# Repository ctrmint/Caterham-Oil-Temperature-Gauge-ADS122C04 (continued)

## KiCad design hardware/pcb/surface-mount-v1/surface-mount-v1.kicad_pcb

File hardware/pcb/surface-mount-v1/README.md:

# surface-mount-v1: interface PCB

surface-mount-v1 is the first interface PCB. It's a two-layer board with surface-mount parts, fitted by the board house. It replaces both the veroboard and the separate protection board. It holds:
- the ADS1115 as a bare chip;
- Rp;
- the three input filters;
- the harness protection;
- the I²C pull-ups;
- the 5 V feed.

It plugs straight into the 8-way socket on the back of the Waveshare case, and the case's two bottom screws hold it on. Issue #48.

**Status:** designed, with zero ERC and zero DRC findings. Not yet built or tested; the fit check and bench checks below are owed. Like the rest of the gauge, it's supplementary to the factory warnings ([docs/SAFETY.md](../../../docs/SAFETY.md)).

| | |
|---|---|
| Size | 39 × 23 mm, 783 mm². D-shaped so it sits 1 mm inside the 51 mm case outline: nothing shows around the gauge. For comparison, the veroboard is 66 × 43 mm. |
| Stack-up | 2 layers, 1.6 mm FR-4, 1 oz copper, GND pour on both sides |
| Rules | 0.2 mm clearance, 0.25 mm minimum track, 0.6/0.3 mm vias, 0.5 mm copper to edge. Well inside a standard JLCPCB or PCBWay 2-layer service. |
| Parts | 20 on the board. The board house fits 17 SMD parts; you fit J1, J2 and Rp. |
| Height above the case back | 2.54 mm spacing, then the board, then the J2 header (9.9 mm) and the harness plug |

## Design decisions (from #48)

1. **Vehicle power: a separate automotive 12 V → 5 V converter.** Its 5 V comes in on J2 pin 3 and passes through D4 (SS34) to the display's 5V pin.
   - The display board wires that pin straight to USB-C VBUS and to the AXP2101's input, with no diode (Waveshare schematic).
   - D4 stops USB power feeding back into the converter when both are connected.
   - D4 drops about 0.4 V, which leaves the display inside its 3.9–5.5 V VBUS range.
2. **Mounting: plugged straight into the case socket.** The case's two bottom screws hold the board, through H1/H2, with 2.5 mm spacers.
3. **Protection: PR #34's design, in surface-mount parts.**
   - Each harness tap is two stages: R3/R5 (1 kΩ, 1206), then a BAV99 clamp to 3.3 V and GND, then R4/R6 (1 kΩ). The BAV99 is a 1N4148-class pair, so it leaks nanoamps, not the microamps of a warm Schottky.
   - An SMBJ15A TVS sits on the signal wire. Its breakdown is at least 16.7 V, so it doesn't conduct at 14.4 V.
   - The 100 kΩ break-detect bias stays on the harness side.
4. **Assembly: the board house fits the SMD parts.** The fab files include a JLCPCB-format BOM and placement file. You fit J1, J2 and Rp.
5. **3.3 V for the ADC and Rp: still the display's 3.3V pin, not a local regulator.** I recommended a local regulator in #48 and have reversed that.
   - A wire chafed onto 14.4 V pushes current back into the 3.3 V rail through Rp and the clamps, about 34 mA for the signal wire.
   - A regulator can only source current, so a lightly loaded local rail would rise with the fault and would need its own clamp.
   - The display's rail is the AXP2101's 2 A DCDC1, and the display board's own load absorbs that current.
   - The rail still sees the fault while the gauge is off; see what this board doesn't cover, below.

## Circuit

The measurement is the one in [WIRING.md](../../WIRING.md): Vp = A0 − A3 across Rp, Vs = A3 − A1 across the sender, and Rs = Rp × Vs / Vp. The differences from the veroboard:
- **Every tap is a soldered track.** There's no plug-in module, so the open-tap failure in #39 (a module socket contact lifting) can't happen here.
- **The board carries its own I²C pull-ups (10 kΩ) and 100 nF decoupling.** The display board has no pull-ups on GPIO17/18, and the Adafruit module used to supply them.
- **R2, the A0 tap, is a Kelvin connection to Rp's top pad.** It runs on its own bottom-layer track and joins nothing else on the way.
- **Nothing is in series between Rp and the sender pin.**
- **R7 biases the sense wire on the harness side of R5**, so a broken sense wire still reads `GROUND FAULT`.

`tests/test_surface_mount_v1.py` checks these rules against the design table, and checks J1 against the firmware's pins.

**With a harness wire at 14.4 V:**

| Wire | Into the 3.3 V rail | Dissipation | Into the ADC pin |
|---|---|---|---|
| Signal | about 24 mA through Rp, plus about 10 mA through R3 and D1 | R1 0.26 W (TNPW1206 is rated 0.27 W at film ≤125 °C); R3 0.11 W (1206, 0.25 W) | under 0.5 mA, through R4 |
| Sense | about 10 mA through R5 and D2 | R5 0.11 W | under 0.5 mA, through R6 |

After any such fault, measure Rp again.

## Connectors

The parts list is [BOM.md](BOM.md), also as `surface-mount-v1-bom.csv`. It gives every part with its manufacturer part number, and both connector pinouts.

- **J1, the display header** (Samtec TSW-108-07-G-S, gold):
  - It's fitted on the **bottom** side: its long pins point away from the components and into the case socket.
  - The pin order matches the case label, 18 17 16 RX TX 3.3V G 5V, which is also printed on the top silkscreen.
  - Pin 1 ("18", SCL) has the square pad.
- **J2, the harness** (Molex Micro-Fit 3.0 43650-0415, 1×4 vertical, positive latch):
  - Pins: 1 sender signal, 2 GND, 3 5 V in, 4 ground sense.
  - The mating housing is 43645-0400 with tin 43030 terminals. They take 0.5 mm² (20 AWG) wire with 1.42–1.85 mm insulation; crimp them with the Molex 63819-0000 or a Micro-Fit ratchet crimper.
  - Twist the sender and sense wires together (WIRING.md).

## Fit check before ordering (human)

The positions come from Waveshare's drawing of the cased board (`ESP32-S3-Touch-AMOLED-1.75-B`), not from your unit. Check them with calipers first:

1. **Socket row:** the 8 pins at 2.54 mm pitch, centred left to right, with their centres 18.70 mm below the case centre. Is the socket face flush with the case back? J1's insulator sets a 2.54 mm gap, so a socket that stands proud changes the spacer height.
2. **Bottom screws:** at ±13.75 mm, 14.70 mm below centre.
   - Check they're M2, and measure the length of the originals.
   - The new screws are that length plus 1.6 mm for the board plus the spacer, so they engage the standoffs as far as before and no further.
3. **Overlay check:** print [renders/placement.svg](renders/placement.svg) at 100 % (1 mm grid, case centre at 0,0), or the Gerbers, and lay it on the case back.

If anything differs, change `layout.py` (`J1_Y`, `HOLES`) and rebuild.

## Ordering and assembly

1. **PCB:** upload `fab/surface-mount-v1-gerbers.zip`. Choose 2 layers, 1.6 mm, any colour, and lead-free HASL or ENIG. Five boards is the usual minimum.
2. **Assembly (optional):** top side only. Upload `fab/surface-mount-v1-bom-jlcpcb.csv` and `fab/surface-mount-v1-cpl-jlcpcb.csv`.
   - Board houses and KiCad differ in the zero rotation for some packages, so check every part in the placement preview: U1's pin-1 dot, the stripes on D3 and D4, and the BAV99s.
   - The files leave out J1, J2 and R1.
3. **Hand-fit R1** (Vishay TNPW1206470RBEEA; Digi-Key or Mouser). Measure it first and note the value: it goes in `kPullUpOhms`, with approval (#36).
4. **Hand-fit J2** on the top side.
5. **Hand-fit J1** from the bottom side and solder it on the top.

## Bench checks (human, owed; see docs/VALIDATION.md)

**Readings through the board:**
- Wire a known 120 Ω resistor from J2 pin 1 to a "tank" point, and connect J2 pins 2 and 4 to the same point.
- Then run WIRING.md bench steps 4–10, with J2 standing in for the harness.

**Fault tests:** apply 14.4 V through a 50 mA current limit to J2 pin 1, then to pin 4. Expect no damage and a fault display, and readings that come back correct afterwards (PR #34).

**Retention:** shake test with the screws and spacers fitted.

## What this board doesn't cover

- **A wire chafed onto an always-live feed while the gauge is off** back-powers the 3.3 V rail through Rp.
- **A long load dump on a wire chafed onto the battery feed** can destroy the TVS. If the TVS then fails short, the gauge shows `SENSOR SHORT`.
- **J1 is still a plug contact.** A bad SDA or SCL contact shows as ADC errors (`adc_ok = false`). A bad 3.3V or GND contact shows as supply or ADC faults.
- **It isn't qualified for automotive use.** The bench checks above and the in-car tests (#43) come first.

## What's in this folder

| Path | What it is |
|---|---|
| `README.md` | This page: decisions, fit check, ordering, assembly, checks. Hand-written. |
| `BOM.md`, `surface-mount-v1-bom.csv` | The full parts list: the board, connectors, harness parts and fitting hardware |
| `fab/surface-mount-v1-gerbers.zip` | Gerbers and drill files, to upload to the board house |
| `fab/surface-mount-v1-bom-jlcpcb.csv`, `fab/surface-mount-v1-cpl-jlcpcb.csv` | The board house's assembly BOM and placement file (SMD parts only) |
| `renders/` | `top.png`, `bottom.png`, `iso.png` (3D); `schematic.svg`; `placement.svg` (1 mm grid in case coordinates) |
| `surface-mount-v1.kicad_pro`, `.kicad_sch`, `.kicad_pcb` | The KiCad 10 project |
| `3d/` | The simplified 3D model of J2, for the renders |
| `generator/` | The source: `design.py` (parts, nets, part numbers) and `layout.py` (placement, routing, silkscreen) |
| `build.sh`, `outputs.sha256` | The rebuild script and the hash manifest it writes |

## Rebuilding

`build.sh` (in this folder) regenerates everything here from `generator/`:
- the KiCad schematic and board;
- ERC and DRC, with schematic parity and zone refill. Any finding fails the build.
- the renders, the Gerbers and drill files, the placement file and the BOMs;
- `outputs.sha256`.

It runs KiCad 10.0.8 in its official container through podman or docker; set `KICAD_LOCAL=1` to use a local KiCad 10.0.8. An unchanged design rebuilds byte-for-byte, so a diff means the design changed.

`tests/test_surface_mount_v1.py`, which runs in CI, fails if anything listed in `outputs.sha256` changes without a rebuild.

**Where the design lives:**
- `design.py`: the parts, nets and part numbers.
- `layout.py`: placement, routing and silkscreen, in case coordinates. `renders/placement.svg` shows the same coordinates.

The generator is the source for surface-mount-v1. You can open the KiCad files in KiCad 10, but the next build overwrites them. To take the design over in the KiCad GUI, delete `generator/` and the generator steps from the script.

KiCad has no 3D model for the Micro-Fit header. `3d/Molex_43650-0415_envelope.wrl` is a plain box of the right size for the renders, not Molex's model.

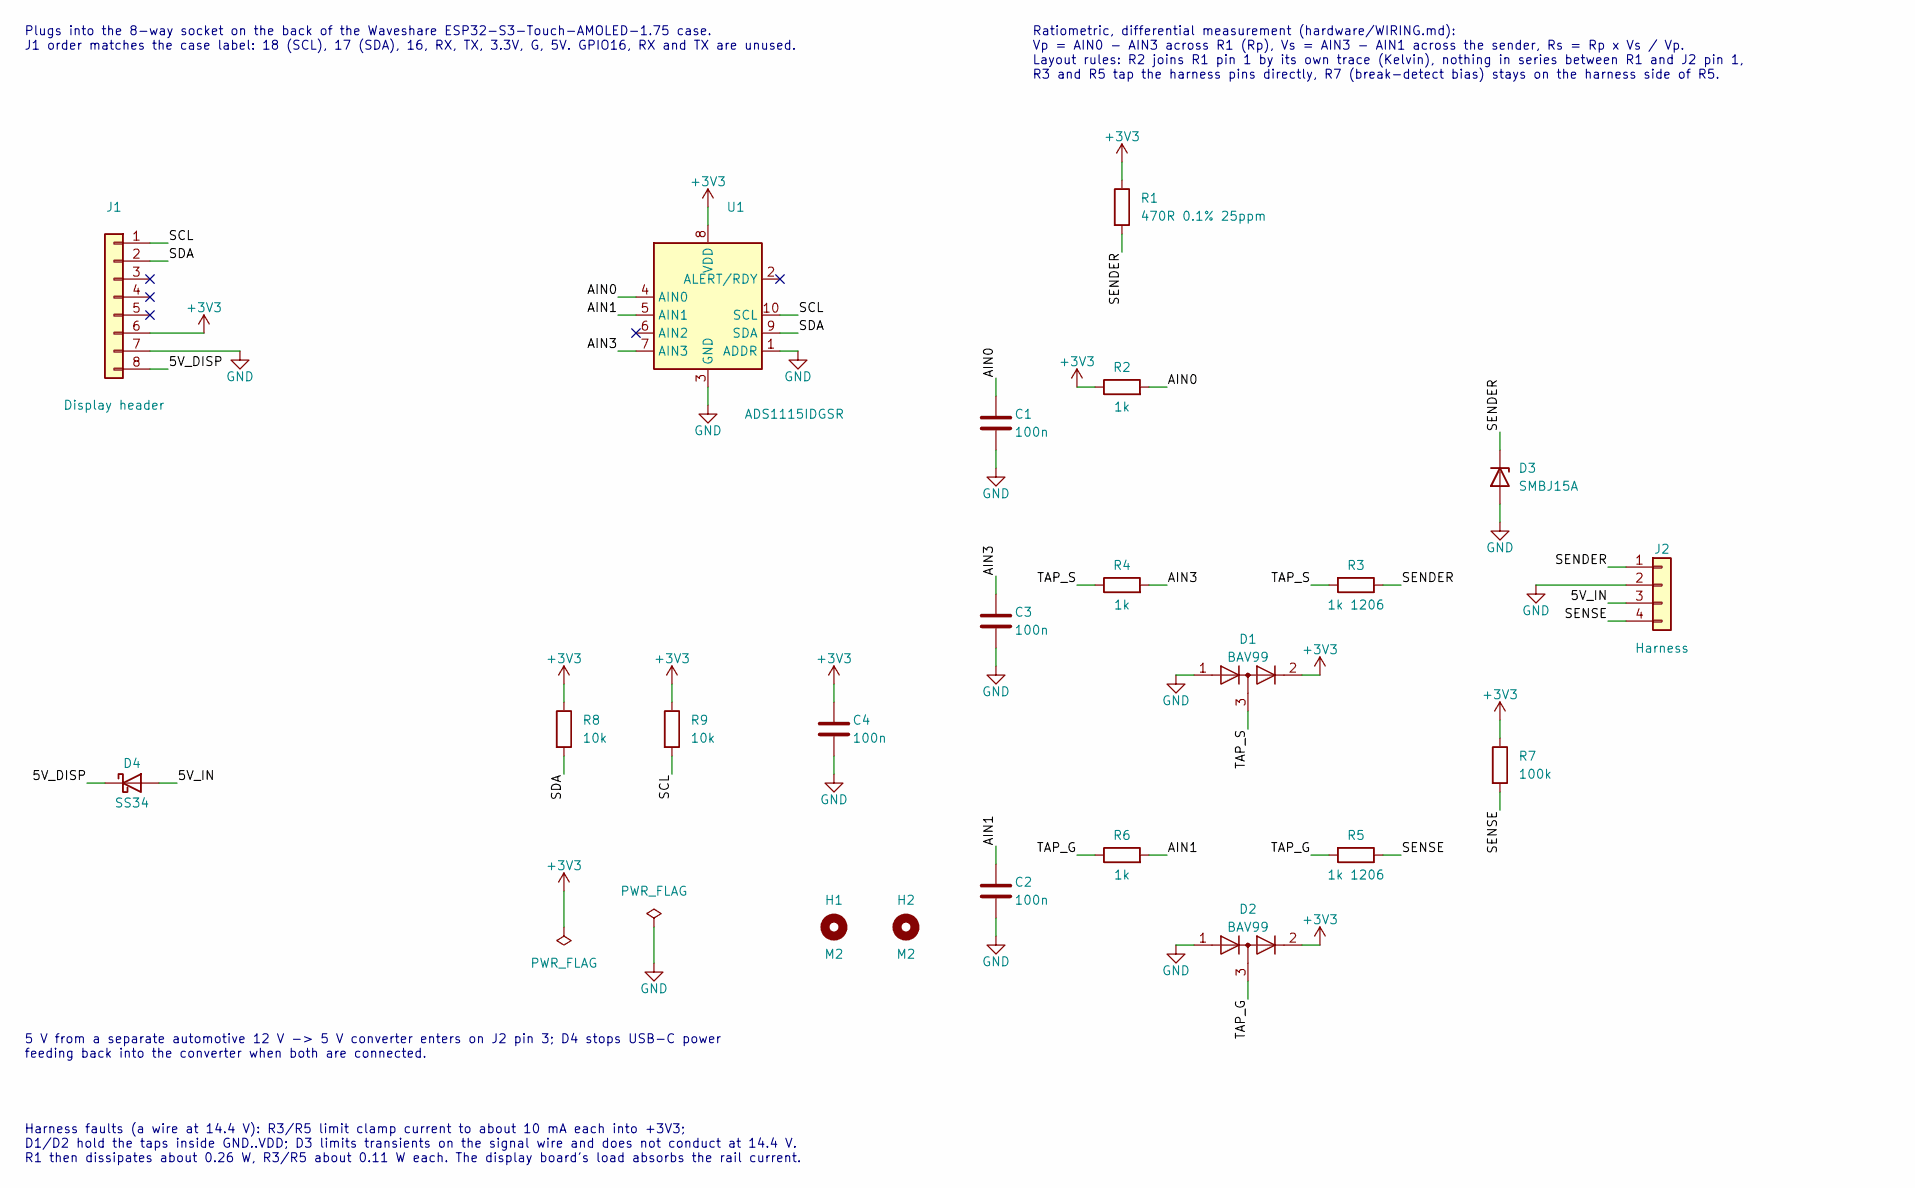
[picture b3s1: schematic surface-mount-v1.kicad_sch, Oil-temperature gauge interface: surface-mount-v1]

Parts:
C1, C2, C3, C4: 100n; C_0603_1608Metric; MPN CC0603KRX7R9BB104; LCSC C14663
D1, D2: BAV99; SOT-23; MPN BAV99,215; LCSC C2500
D3: SMBJ15A; D_SMB; MPN SMBJ15A; LCSC C83846
D4: SS34; D_SMA; MPN SS34; LCSC C8678
H1, H2: M2; MountingHole_2.2mm_M2
J1: Display header; PinHeader_1x08_P2.54mm_Vertical; MPN TSW-108-07-G-S; LCSC C3335496
J2: Harness; Molex_Micro-Fit_3.0_43650-0415_1x04_P3.00mm_Vertical; MPN 43650-0415; LCSC C293547
R1: 470R 0.1% 25ppm; R_1206_3216Metric; MPN TNPW1206470RBEEA
R2, R4, R6: 1k; R_0603_1608Metric; MPN 0603WAF1001T5E; LCSC C21190
R3, R5: 1k 1206; R_1206_3216Metric; MPN 1206W4F1001T5E; LCSC C4410
R7: 100k; R_0603_1608Metric; MPN 0603WAF1003T5E; LCSC C25803
R8, R9: 10k; R_0603_1608Metric; MPN 0603WAF1002T5E; LCSC C25804
U1: ADS1115IDGSR; TSSOP-10_3x3mm_P0.5mm; MPN ADS1115IDGSR; LCSC C37593

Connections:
+3V3: C4.1, D1.2 (A), D2.2 (A), J1.6, R1.1, R2.1, R7.1, R8.1, R9.1, U1.8 (VDD)
/5V_DISP: D4.1 (K), J1.8
/5V_IN: D4.2 (A), J2.3
/AIN0: C1.1, R2.2, U1.4 (AIN0)
/AIN1: C2.1, R6.2, U1.5 (AIN1)
/AIN3: C3.1, R4.2, U1.7 (AIN3)
/SCL: J1.1, R9.2, U1.10 (SCL)
/SDA: J1.2, R8.2, U1.9 (SDA)
/SENDER: D3.1 (K), J2.1, R1.2, R3.1
/SENSE: J2.4, R5.1, R7.2
/TAP_G: D2.3 (K), R5.2, R6.1
/TAP_S: D1.3 (K), R3.2, R4.1
GND: C1.2, C2.2, C3.2, C4.2, D1.1 (K), D2.1 (K), D3.2 (A), J1.7, J2.2, U1.1 (ADDR), U1.3 (GND)

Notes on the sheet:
Plugs into the 8-way socket on the back of the Waveshare ESP32-S3-Touch-AMOLED-1.75 case. J1 order matches the case label: 18 (SCL), 17 (SDA), 16, RX, TX, 3.3V, G, 5V. GPIO16, RX and TX are unused.
Harness faults (a wire at 14.4 V): R3/R5 limit clamp current to about 10 mA each into +3V3; D1/D2 hold the taps inside GND..VDD; D3 limits transients on the signal wire and does not conduct at 14.4 V. R1 then dissipates about 0.26 W, R3/R5 about 0.11 W each. The display board's load absorbs the rai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
5 V from a separate automotive 12 V -> 5 V converter enters on J2 pin 3; D4 stops USB-C power feeding back into the converter when both are connected.
Ratiometric, differential measurement (hardware/WIRING.md): Vp = AIN0 - AIN3 across R1 (Rp), Vs = AIN3 - AIN1 across the sender, Rs = Rp x Vs / Vp. Layout rules: R2 joins R1 pin 1 by its own trace (Kelvin), nothing in series between R1 and J2 pin 1, R3 and R5 tap the harness pins directly, R7 (brea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

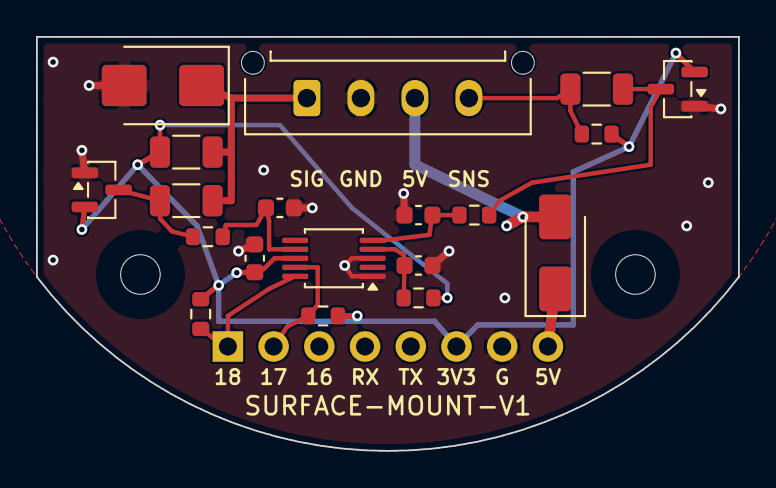
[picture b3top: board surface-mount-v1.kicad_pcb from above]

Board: 2 copper layers, 39.0 x 23.0 mm, 22 parts (1 on the bottom side), 13 nets.

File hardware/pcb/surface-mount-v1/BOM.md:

# surface-mount-v1: parts list

Every part for the surface-mount-v1 interface board and its harness. The same list is in `surface-mount-v1-bom.csv`, and the board-house subset in `fab/surface-mount-v1-bom-jlcpcb.csv`.

Generated by `generator/outputs.py` from `generator/design.py`; edit that, not this file, then run `build.sh`. Part numbers were checked against manufacturer datasheets and distributor pages on 2026-11-15. LCSC numbers are for the board house's assembly service; `hand` parts are fitted by you (see README.md).

## On the board

| Ref | Qty | Value | Package | Manufacturer | MPN | LCSC | Fit | Notes |
|---|---:|---|---|---|---|---|---|---|
| J1 | 1 | Display header | 1x08 2.54 mm THT (bottom side) | Samtec | `TSW-108-07-G-S` | C3335496 | hand | 8-way 2.54 mm pin header, gold, plugs into the display case socket |
| J2 | 1 | Harness | Micro-Fit 1x04 vertical THT | Molex | `43650-0415` | C293547 | hand | Micro-Fit 3.0 1x4 vertical header, tin; mates with housing 43645-0400 and tin 43030 terminals |
| U1 | 1 | ADS1115IDGSR | VSSOP-10 (TSSOP-10 3x3) | Texas Instruments | `ADS1115IDGSR` | C37593 | board house | 16-bit I2C ADC, VSSOP-10 |
| R1 | 1 | 470R 0.1% 25ppm | 1206 | Vishay | `TNPW1206470RBEEA` | - | hand | Rp: 470R 0.1% 25ppm/K thin film, 1206, 0.27 W (P70, film <=125 C), AEC-Q200 |
| R2, R4, R6 | 3 | 1k | 0603 | UNI-ROYAL | `0603WAF1001T5E` | C21190 | board house | 1k 1% 0.1 W 0603 |
| R3, R5 | 2 | 1k 1206 | 1206 | UNI-ROYAL | `1206W4F1001T5E` | C4410 | board house | 1k 1% 0.25 W 1206 (fault dissipation about 0.11 W) |
| R7 | 1 | 100k | 0603 | UNI-ROYAL | `0603WAF1003T5E` | C25803 | board house | 100k 1% 0.1 W 0603 |
| R8, R9 | 2 | 10k | 0603 | UNI-ROYAL | `0603WAF1002T5E` | C25804 | board house | 10k 1% 0.1 W 0603 |
| C1, C2, C3, C4 | 4 | 100n | 0603 | Yageo | `CC0603KRX7R9BB104` | C14663 | board house | 100n 50 V X7R 0603 |
| D1, D2 | 2 | BAV99 | SOT-23 | Nexperia | `BAV99,215` | C2500 | board house | Series switching-diode pair, SOT-23 |
| D3 | 1 | SMBJ15A | SMB | Littelfuse | `SMBJ15A` | C83846 | board house | TVS 600 W, 15 V standoff, unidirectional, SMB |
| D4 | 1 | SS34 | SMA | MDD | `SS34` | C8678 | board house | Schottky 40 V 3 A, SMA |

## Connectors and fitting (not on the board)

| Item | Qty | Manufacturer | MPN | LCSC | Notes |
|---|---:|---|---|---|---|
| Harness plug housing (mates with J2) | 1 | Molex | `43645-0400` | C277618 | Micro-Fit 3.0 receptacle, 1x4, single row |
| Crimp terminals for the housing | 4 (+spares) | Molex | `43030-0007` | - | Tin, loose piece, to match J2's tin header; 20-24 AWG (0.5-0.2 mm2), insulation OD 1.42-1.85 mm. 43030-0001 (LCSC C259786) is the same terminal on a reel |
| Crimp tool for the terminals | 1 | Molex | `63819-0000` | - | Ratcheting, 20-30 AWG. Molex only guarantees its crimp spec with Molex tooling; a third-party Micro-Fit ratchet crimper also works |
| Retaining screws | 2 | - | `M2 pan head, A2 stainless` | - | Replace the case's two bottom screws: same thread, longer by the board (1.6 mm) plus the spacer. Measure the original screws first |
| Spacers | 2 | - | `M2 nylon spacer, 2.5 mm` | - | Between the board and the case back at H1/H2; matches J1's 2.54 mm insulator. Confirm at the fit check |
| Harness wire | as needed | - | `0.5 mm2 (20 AWG)` | - | Signal and ground-sense twisted together (or 2-core screened, screen grounded at the gauge end); 5 V and GND from the converter |
| 12 V to 5 V automotive converter | 1 | - | `not specified here` | - | Fused ignition feed, cranking/load-dump/reverse-polarity rated (hardware/BOM.md); its 5 V goes to J2 pin 3 |

## Connector pinouts

**J1, display header** (bottom side, plugs into the case socket; order as on the case label, left to right seen from the back):

| J1 pin | Case label | Net | Use |
|---:|---|---|---|
| 1 | 18 | SCL | I2C SCL (GPIO18) |
| 2 | 17 | SDA | I2C SDA (GPIO17) |
| 3 | 16 | - | Not connected |
| 4 | RX | - | Not connected |
| 5 | TX | - | Not connected |
| 6 | 3.3V | +3V3 | ADC supply and Rp excitation |
| 7 | G | GND | Ground |
| 8 | 5V | 5V_DISP | Display 5 V (VBUS) from D4 |

**J2, harness** (Micro-Fit 3.0, 1x4):

| J2 pin | Net | Wire to |
|---:|---|---|
| 1 | SENDER | Sender spade terminal (signal) |
| 2 | GND | Gauge supply ground / chassis, near the tank bond |
| 3 | 5V_IN | 5 V from the automotive converter |
| 4 | SENSE | Ground-sense wire to the tank bond stud |
